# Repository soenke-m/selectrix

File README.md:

# selectrix

Ich baue und entwickle Hard- und Software für das Selectrix-System

Hier möchte ich gerne meine SX-Projeke  mit euch Teilen damit alle die Selectrix einsetzen wollen davon profitieren können.

Die Projekte basieren auf den Atmel ATtiny Microcontroler und sind mit Atmel Studio 7 erstellt. 
Zum Testen steht mir eine FCC zur Verfügung.

Der Nachbau und die Benutzung der Hardware geschieht auf eigene Gefahr, ich hafte nicht für Schäden, die der Anwender oder Dritte durch die Verwendung verursachen.

Alle Daten sind lizensiert unter der <a href="http://creativecommons.org/licenses/by-nc-sa/4.0/">Attribution-NonCommercial-ShareAlike 4.0 International</a>. - die eine private Weiterverwertung erlaubt, solange in angemessener Weise die Urheberschaft erwähnt wird und die abgeleitete Arbeit unter der gleichen Lizenz steht.

<br />Dieses Werk ist lizenziert unter einer <a rel="license" href="http://creativecommons.org/licenses/by-nc-sa/4.0/">Creative Commons Namensnennung - Nicht-kommerziell - Weitergabe unter gleichen Bedingungen 4.0 International Lizenz</a>.

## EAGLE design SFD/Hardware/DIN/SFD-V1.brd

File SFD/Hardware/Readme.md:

Dieser Ordner enthält die Eagle Dateien

Die DIN-Stecker Version ist eine einseitige Platine

Es existiert ein <a href="https://www.reichelt.de/my/1683631">Reichel Warenkorb</a>. Die Teileliste ist für beide Versionen gültig. Die nicht benötigten Teile müssen dann gelöscht werden.

Das Gehäuseoberteil muss an den Längsseiten um 4mm gekürzt werden. Die Schraubendome müssen auf dieses Niveau abgefeilt werden. Die Platine wird dann zwischen beide Gehäusehälften eingeklemmt.

Das Bild zeigt noch den Prototyp mit Lochstreifenplatine.

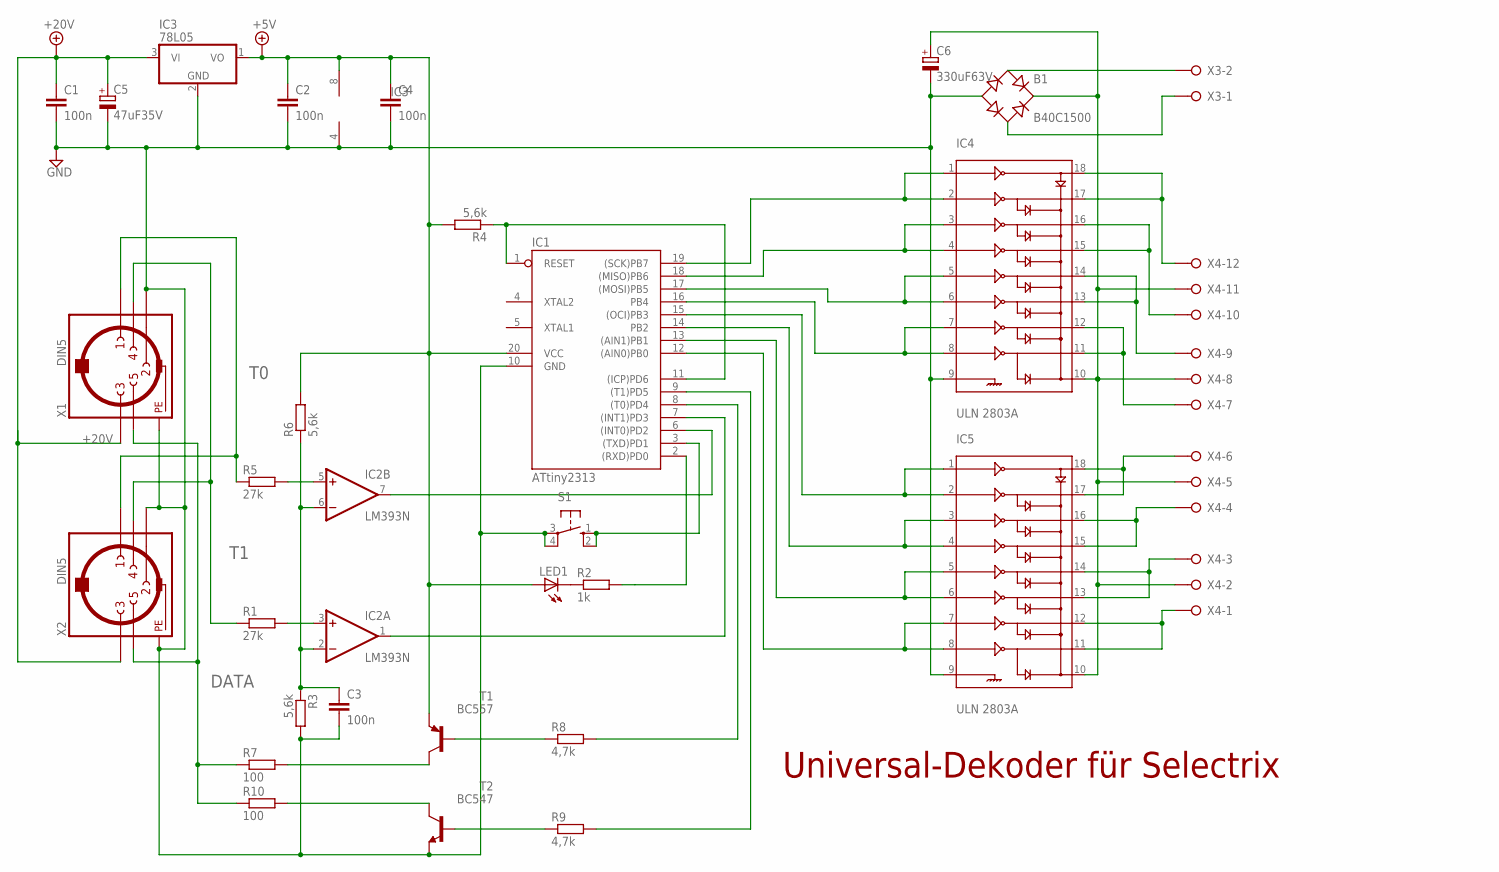
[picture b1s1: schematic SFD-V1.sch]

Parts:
B1: B40C1500; RB1A
C1, C2, C3, C4: 100n; C025-025X050
C5: 47uF35V; E2,5-6E
C6: 330uF63V; E5-13
IC1: ATtiny2313; DIL20
IC2: LM393N; DIL08
IC3: 78L05; TO92
IC4, IC5: ULN 2803A; DIL18
LED1: LED3MM
R1, R5: 27k; 0207/10
R2: 1k; 0207/10
R3, R4, R6: 5,6k; 0207/10
R7, R10: 100; 0207/10
R8, R9: 4,7k; 0207/10
S1: 10-XX; B3F-10XX
T1: BC557; TO92
T2: BC547; TO92
X1, X2: DIN5; CON-HIRSCHMANN_DIN5
X3: W237-02P; W237-132
X4: W237-12P

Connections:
2-INT0: IC1.6 ((INT0)PD2), IC2.7 (OUT)
4: IC1.7 ((INT1)PD3), IC2.1 (OUT)
+5V: C2.1, C4.1, IC1.20 (VCC), IC2.8 (V+), IC3.1 (VO), LED1.A, R4.2, R6.2, T1.1 (E)
+20V: C1.1, C5.+, IC3.3 (VI), X1.3, X2.3
DATA: R7.1, R10.1, X1.5, X2.5
GND: B1.-, C1.2, C2.2, C3.2, C4.2, C5.-, C6.-, IC1.10 (GND), IC2.4 (V-), IC3.2 (GND), IC4.9, IC5.9, R3.2, S1.3, S1.4 (P1), T2.1 (E), X1.2, X1.PE, X1.PE1 (PE), X1.PE@ (PE), X1.PE@1 (PE), X2.2, X2.PE, X2.PE1 (PE), X2.PE@ (PE), X2.PE@1 (PE)
unnamed: IC1.3 ((TXD)PD1), S1.1 (S), S1.2 (S1)
unnamed: IC1.8 ((T0)PD4), R8.2
unnamed: B1.AC1, X3.2
unnamed: IC2.5 (+IN), R5.2
unnamed: IC2.3 (+IN), R1.2
unnamed: LED1.K (C), R2.1
unnamed: C3.1, IC2.2 (-IN), IC2.6 (-IN), R3.1, R6.1
unnamed: IC1.2 ((RXD)PD0), R2.2
unnamed: IC1.1 (RESET), IC1.11 ((ICP)PD6), R4.1
unnamed: IC1.12 ((AIN0)PB0), IC5.7, IC5.8
unnamed: IC1.13 ((AIN1)PB1), IC5.5, IC5.6
unnamed: IC1.14 (PB2), IC5.3, IC5.4
unnamed: R10.2, T2.3 (C)
unnamed: IC1.15 ((OCI)PB3), IC5.1, IC5.2
unnamed: B1.AC2, X3.1
unnamed: R7.2, T1.3 (C)
unnamed: IC1.16 (PB4), IC4.7, IC4.8
unnamed: IC1.17 ((MOSI)PB5), IC4.5, IC4.6
unnamed: IC4.17, IC4.18, X4.12
unnamed: IC1.19 ((SCK)PB7), IC4.1, IC4.2
unnamed: IC1.18 ((MISO)PB6), IC4.3, IC4.4
unnamed: B1.+, C6.+, IC4.10, IC5.10, X4.2, X4.5, X4.8, X4.11
unnamed: IC1.9 ((T1)PD5), R9.2
unnamed: IC4.15, IC4.16, X4.10
unnamed: R8.1, T1.2 (B)
unnamed: IC4.13, IC4.14, X4.9
unnamed: R9.1, T2.2 (B)
unnamed: IC4.11, IC4.12, X4.7
unnamed: IC5.17, IC5.18, X4.6
unnamed: IC5.15, IC5.16, X4.4
unnamed: IC5.13, IC5.14, X4.3
unnamed: IC5.11, IC5.12, X4.1
T0: R5.1, X1.1, X2.1
T1: R1.1, X1.4, X2.4

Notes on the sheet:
Universal-Dekoder für Selectrix
IC3

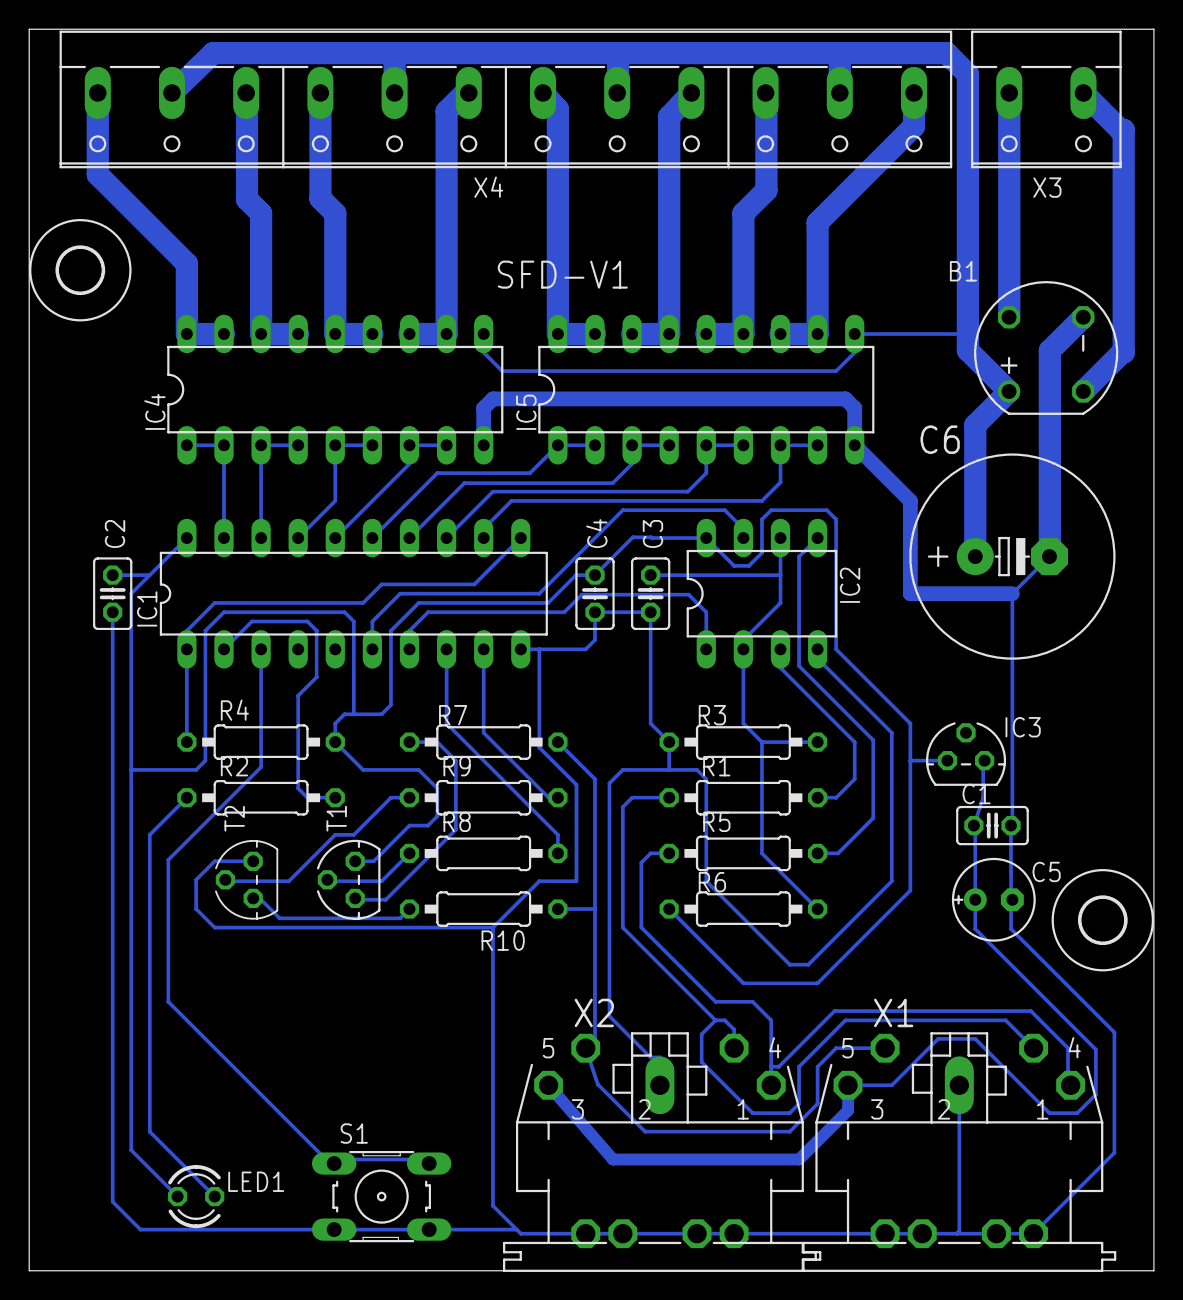
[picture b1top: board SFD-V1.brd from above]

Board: 2 copper layers, 77.0 x 85.0 mm, 32 parts (0 on the bottom side), 40 nets.

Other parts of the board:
U$1, U$2: 3,0

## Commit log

2020-05-01 SFD-Projekt hinzugefügt
2020-05-01 Bug beseitigt (falsche Pinzuordnung)
2020-05-02 Aktualisiert
2020-05-02 Update Doku
2020-05-02 DecProg online gestellt
